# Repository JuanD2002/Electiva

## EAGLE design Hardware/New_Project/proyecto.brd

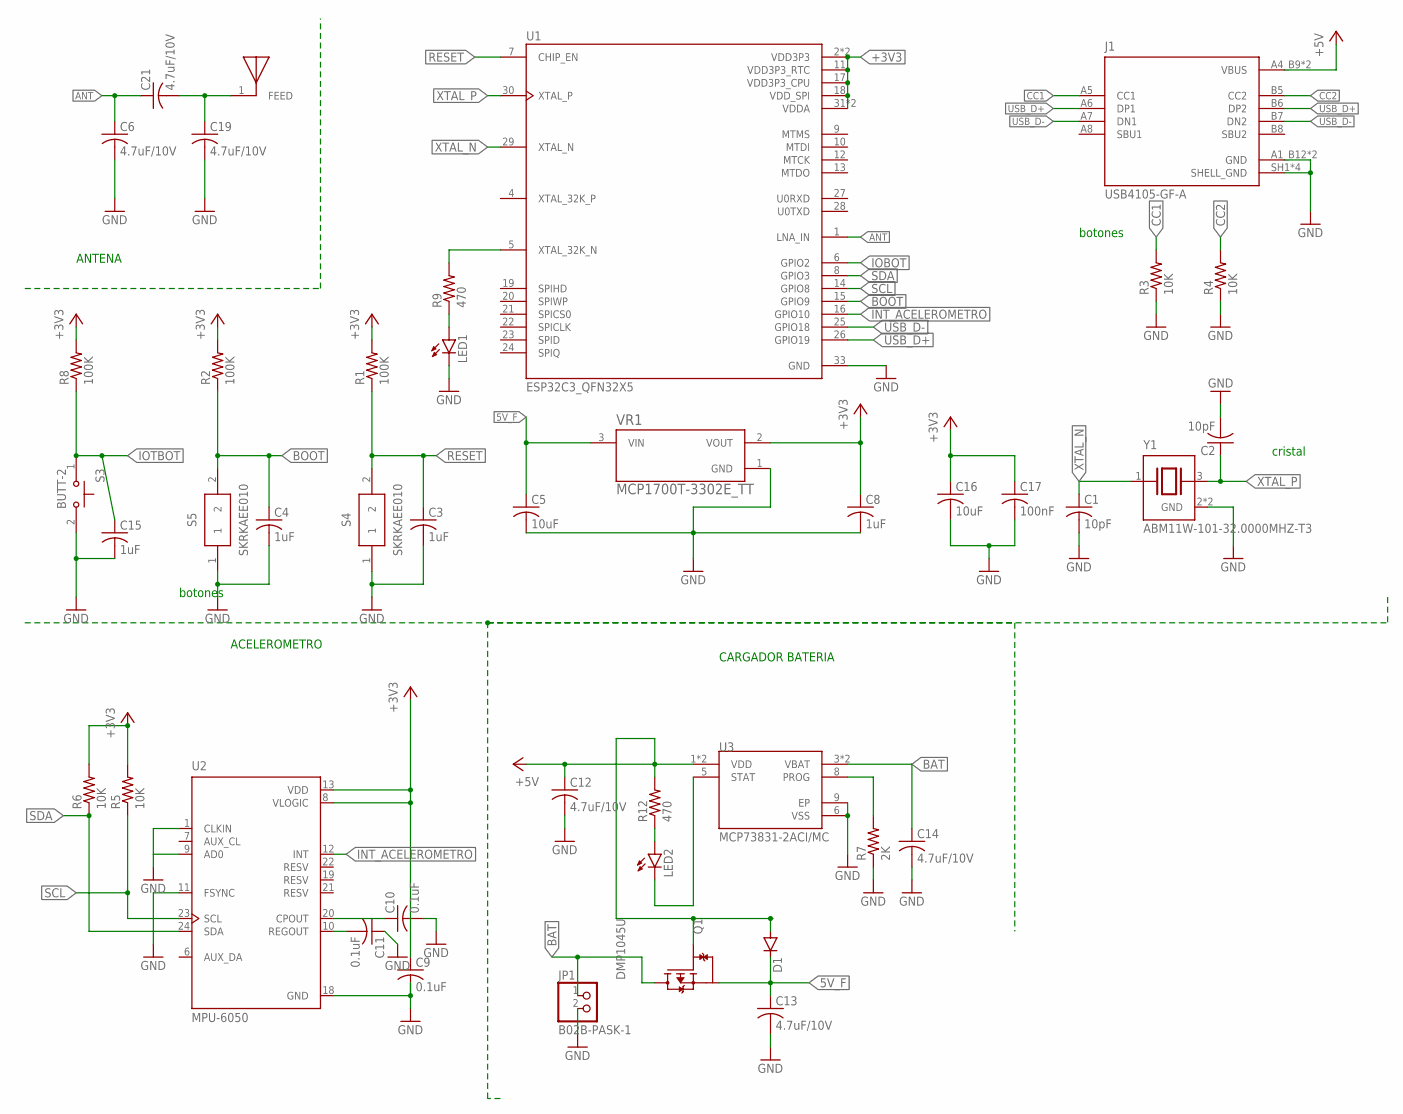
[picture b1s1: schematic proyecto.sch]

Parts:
C1, C2: 10pF; C0603
C3, C4, C8, C15: 1uF; C0603
C5, C16: 10uF; C0603
C6, C12, C13, C14, C19, C21: 4.7uF/10V; C0603
C9, C10, C11: 0.1uF; C0603
C17: 100nF; C0603
D1: DIODE-DO214AA; DO214AA
J1: USB4105-GF-A; GCT_USB4105-GF-A
JP1: B02B-PASK-1
LED1, LED2: LEDSML0603; SML0603
Q1: DMP1045U; SOT91P240X110-3N
R1, R2, R8: 100K; R0603
R3, R4, R5, R6: 10K; R0603
R7: 2K; R0603
R9, R12: 470; R0603
S3: BUTT-2; SW_BUTT-2
S4, S5: SKRKAEE010; SKRK
U1: ESP32C3_QFN32X5; QFN32_5X5MM
U2: MPU-6050; QFN50P400X400X95-24N
U3: MCP73831-2ACI/MC; SON50P200X300X100-9N
U$1: RFANT5220110A0T; ANTENA
VR1: MCP1700T-3302E_TT; SOT95P237X112-3N
Y1: ABM11W-101-32.0000MHZ-T3; XTAL_ABM11W-101-32.0000MHZ-T3

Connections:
5V_F: C5.1, C13.1, D1.C, Q1.2 (S), VR1.3 (VIN)
+3V3: C8.1, C9.1, C16.1, C17.1, R1.2, R2.2, R5.2, R6.2, R8.2, U1.2 (VDD3P3), U1.3 (VDD3P3), U1.11 (VDD3P3_RTC), U1.17 (VDD3P3_CPU), U1.18 (VDD_SPI), U1.31 (VDDA), U1.32 (VDDA), U2.8 (VLOGIC), U2.13 (VDD), VR1.2 (VOUT)
+5V: C12.1, D1.A, J1.A4_B9 (VBUS), J1.B4_A9 (VBUS), Q1.1 (G), R12.2, U3.1 (VDD), U3.2 (VDD)
+5V1: R9.2, U1.5 (XTAL_32K_N)
ANT: C6.1, C21.1, U1.1 (LNA_IN)
BAT: C14.1, JP1.1, Q1.3 (D), U3.3 (VBAT), U3.4 (VBAT)
BOOT: C4.1, R2.1, S5.2, U1.15 (GPIO9)
CC1: J1.A5 (CC1), R3.2
CC2: J1.B5 (CC2), R4.2
GND: C1.2, C2.2, C3.2, C4.2, C5.2, C6.2, C8.2, C9.2, C10.2, C11.1, C12.2, C13.2, C14.2, C15.2, C16.2, C17.2, C19.2, J1.A1_B12 (GND), J1.B1_A12 (GND), J1.SH1 (SHELL_GND), J1.SH2 (SHELL_GND), J1.SH3 (SHELL_GND), J1.SH4 (SHELL_GND), JP1.2, LED1.C, R3.1, R4.1, R7.1, S3.2, S4.1, S5.1, U1.33 (GND), U2.1 (CLKIN), U2.9 (AD0), U2.11 (FSYNC), U2.18 (GND), U3.6 (VSS), U3.9 (EP), VR1.1 (GND), Y1.2 (GND), Y1.4 (GND)
INT_ACELEROMETRO: U1.16 (GPIO10), U2.12 (INT)
IOBOT: U1.6 (GPIO2)
IOTBOT: C15.1, R8.1, S3.1
unnamed: LED1.A, R9.1
unnamed: LED2.A, R12.1
unnamed: LED2.C, U3.5 (STAT)
unnamed: R7.2, U3.8 (PROG)
unnamed: C11.2, U2.10 (REGOUT)
unnamed: C10.1, U2.20 (CPOUT)
unnamed: C19.1, C21.2, U$1.1
RESET: C3.1, R1.1, S4.2, U1.7 (CHIP_EN)
SCL: R5.1, U1.14 (GPIO8), U2.23 (SCL)
SDA: R6.1, U1.8 (GPIO3), U2.24 (SDA)
USB_D+: J1.A6 (DP1), J1.B6 (DP2), U1.26 (GPIO19)
USB_D-: J1.A7 (DN1), J1.B7 (DN2), U1.25 (GPIO18)
XTAL_N: C1.1, U1.29 (XTAL_N), Y1.1
XTAL_P: C2.1, U1.30 (XTAL_P), Y1.3 (2)

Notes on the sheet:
ANTENA
CARGADOR BATERIA
ACELEROMETRO
botones
cristal

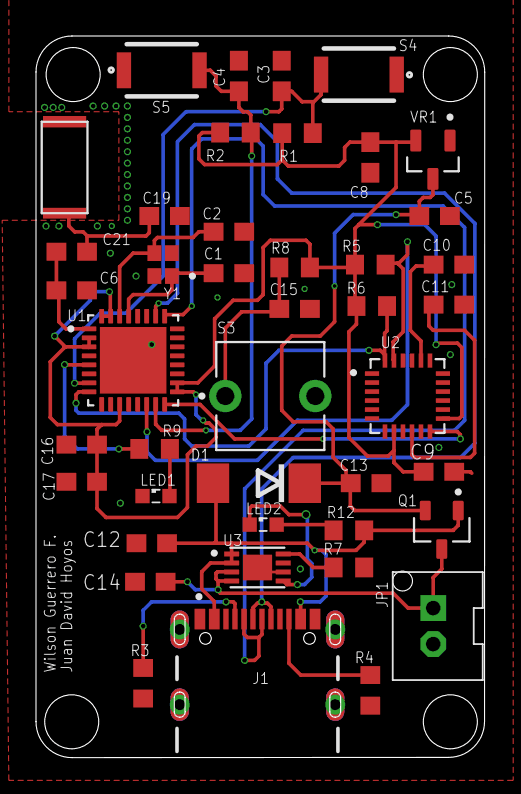
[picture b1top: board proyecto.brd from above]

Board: 2 copper layers, 24.9 x 40.1 mm, 43 parts (0 on the bottom side), 26 nets.

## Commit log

2024-03-29 Se agrega el proyecto
2024-03-29 Se agrega la carpeta Firmware
2024-03-29 Se añade la carpeta Documentacion y Hardware
2024-04-10 Correcciones de pcb
2024-04-25 Se agrega el diseño corregido
2024-05-30 Se agrega el codigo
